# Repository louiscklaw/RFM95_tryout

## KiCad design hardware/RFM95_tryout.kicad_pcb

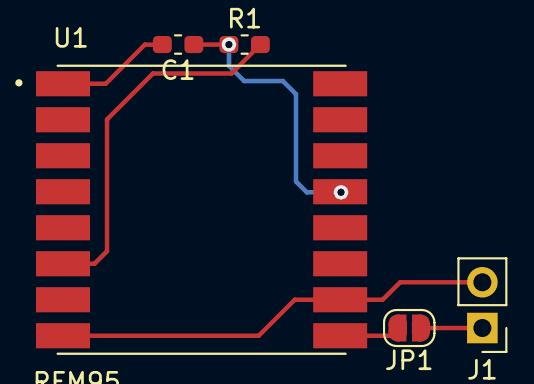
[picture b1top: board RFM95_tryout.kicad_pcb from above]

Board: 2 copper layers, 5 parts (0 on the bottom side), 5 nets.

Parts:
C1: C475,0603; C_0603_1608Metric_Pad1.05x0.95mm_HandSolder
J1: ANT; PinHeader_1x02_P2.54mm_Vertical
JP1: ANT_EN; SolderJumper-2_P1.3mm_Open_RoundedPad1.0x1.5mm
R1: R103,0603; R_0603_1608Metric_Pad1.05x0.95mm_HandSolder
U1: RFM95

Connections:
+3V3: C1.1, R1.1, U1.13
/ANT: JP1.2, U1.9
/RFM_RST: R1.2, U1.6
GND: C1.2, J1.2, U1.1, U1.8, U1.10
unnamed: J1.1, JP1.1

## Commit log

2019-06-13 update,
2020-05-07 ci: init travis build config,
2020-05-07 ci: init travis token,
